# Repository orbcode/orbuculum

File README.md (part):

This is Orbuculum V2.2.0. Bugfixes for 2.2.x will be done in this branch. Development is generally done in feature branches and folded into main as those features mature - those are post 2.2.0.

Version 2.2.0 builds on 2.1.0 and adds several new CPU families, improved client application handling and the start of ETM4 support. Stats and timing are also much improved and the whole communications subsystem has been simplified and streamlined. Most importantly though, we have moved from 'legacy' protocol (basically, the exact same protocol that flows from the chip) for communications to 'orbflow' protocol. Orbflow protocol is an extensible packet oriented protocol which provides a more compact representation of the probe data. By default orbflow is used transparently between orbuculum and client applications. If you have an ORBTrace 1.4.0 or higher version then it is also used for communication from the probe to orbuculum. If you have your own legacy applications, or a version of ORBTrace less that 1.4.0, then the system will fall back to legacy protocol transparently. You can have a hybrid arrangement where some clients use legacy protocol and some use orbflow no problem.  As you might imagine this can quickly become complex so please yell up if any edge cases don't seem to work correctly!

For the full benefit of this version you should be using ORBTrace mini Version 1.4.0 or higher. It will work with earlier versions but you won't get the in probe TPIU stripping or improved probe to host comms protocol support.

The CHANGES file now tells you what's been done recently.

Orbuculum now has an active Discord channel at https://discord.gg/P7FYThy . Thats the place to go if you need interactive help.

An Orbuculum is a Crystal Ball, used for seeing things that would
 be otherwise invisible. A  nodding reference to (the) BlackMagic
 (debug probe), BMP.

You can find information about using this suite at [Orbcode](https://www.orbcode.org), especially the 'Data Feed' section.

**ORBTrace Mini is now available for debug and realtime tracing. Go to [Orbcode](https://www.orbcode.org) for more info.**

The code is in daily use and small issues are patched as they are found. The software runs on Linux, OSX and Windows. Any bugs in a release version are treated as high priority issues. Functional enhancements will also be folded in as time permits. Currently progress is reasonably rapid, and patches are always welcome.

What is it?
===========

Orbuculum is a set of tools for decoding and presenting output flows from
the tracing output pins of a CORTEX-M CPU. Originally it only supported the SWO pin in UART format but it now also
supports hardware for parallel tracing through ORBtrace as well as SWO in UART and Manchester formats.
Numerous types of data can be output through these various
pins, from multiple channels of text messages through to Program Counter samples and even full cycle accurate instruction trace.
Processing these data gives you a huge amount of insight into what is really going on inside
your CPU. The tools are all mix-and-match according to what you are trying to do. The current set is;

* orbuculum: The main mux program which interfaces to the trace probe and then issues a network
interface to which an arbitary number of clients can connect. This is
used as a base interface to the target by other programs in the suite. Generally you configure
this for the TRACE tool you're using and then you can just leave it running. It will grab
data from the target and make it available to clients whenever it can.

* orbcat: A simple cat utility for ITM channel data.

* orbdump: A utility for dumping raw SWO data to a file for post-processing.

* orbmortem: A post mortem analysis tool.

* orbtop: A top utility to see what's actually going on with your target. It can also
generate input files for dot and gnuplot for perty graphics.

* orbtop-rtos: An enhanced version of orbtop with RTOS-aware thread profiling support. Currently
supports  RTOS ( cmsis rtx, etc) and provides per-thread CPU usage statistics, thread state monitoring, and
context switch analysis. Requires connection to OpenOCD for RTOS data extraction.

* orbstat: An analysis/statistics utility which can produce KCacheGrind input files.

* orbtrace: The fpga configuration controller for use with ORBtrace hardware.

* orbzmq: ZeroMQ server.

* orblcd: LCD emulator on the host.

There is also Python support in the [pyorb](https://github.com/orbcode/pyorb) repository.

A few simple use cases are documented in the last section of this
document, as are example outputs from using orbtop to report on the
activity of BMP while emitting SWO packets.

The data flowing from the SWO pin can be encoded
either using NRZ (UART) or RZ (Manchester) formats.  The pin is a
dedicated one that would be used for TDO when the debug interface is
in JTAG mode. We have demonstrated
ITM feeds of around 4.3MBytes/sec on a STM32F427 via SWO with Manchester
encoding running at 48Mbps. SWO with UART encoding is good for 62Mbaud. The encoding of UART
is less efficient than Manchester so those speeds come out largely the same. Users are advised
to use Manchester encoding if their probe supports it because then they don't have to stress about
data speeds (it's autobauding), clock changes or start/stop bits.

The data flowing from the parallel TRACE pins is clocked using a separate TRACECLK pin. There can
be 1-4 TRACE pins which obviously give you much higher bandwidth than the single SWO. Using ORBTrace
we have demonstrated ITM feeds of around 12.5MBytes/sec on a STM32F427 via 4 bit parallel trace. These are not
typos, parallel trace really does run that fast if you've got suitable hardware.

Whatever it's source, orbuculum takes these data flow and makes them accessible to tools on the host
PC. At its core it takes data from the source, decodes it and presents it on a network
interface...both orbflow and legacy protocols are available. The Orbuculum tools don't care if the data
originates from a RZ or NRZ port, SWO or TRACE, or at what speed....that's all the job
of the interface.

At the present time Orbuculum supports ten devices for collecting trace
from the target;

* Black Magic Debug Probe (BMP)
* SEGGER JLink
* generic USB TTL Serial Interfaces
* FTDI High speed serial interfaces
* OpenOCD (Add a line like `tpiu config internal :3443 uart off 32000000` to your openocd config to use it...more detailed configuration info at the bottom of this document)
* PyOCD (Add options like `enable_swv: True`, `swv_system_clock: 32000000` to your `pyocd.yml` to use it.)
* ECPIX-5 ECP5 Breakout Board for parallel trace
* Anything capable of saving the raw SWO data to a file
* Anything capable of offering SWO on a TCP port
* ORBTrace Mini (V1.4.0 or higher for orbflow support)

Note that current support for the ECPIX-5 breakout board is based on the original BOB, the designs for which
are in the orbtrace_hw repository. BOB2 support will be added when we get around to it (probably when we decide we
need USB3 support...unlikely to be yet a while).

For 'normal' users we highly reccomend the ORBTrace mini probe for the best experience using this stuff. That's
not particularlly to make money (the designs are in the orbtrace_hw directory...feel free to build you own), but
because that hardware has been tuned for the job to be done. Getting an ORBTrace allows you to participate in the
project, it's not a product yet, although it does work remarkably well.

gdb setup files for each device type can be found in the `Support` directory. You'll find
example get-you-going applications in the [Orbmule](https://github.com/orbcode/orbmule) repository including
`gdbinit` scripts for OpenOCD, pyOCD and Black Magic Debug Application (BMDA). There are walkthroughs for lots of examples
of the use of the suite at [Orbcode](https://orbcode.org).

When using SWO Orbuculum can use, or bypass, the TPIU. The TPIU adds overhead
to the datastream, but provides better synchronisation if there is corruption
on the link. To include the TPIU in decode stack, provide the -T
option on the orbuculum command line. If you don't provide it, and the ITM decoder sees
TPIU syncs in the datastream, it will complain. This is deliberate
after I spent two days trying to find an obscure bug 'cos I'd left the `-T` option off. If you don't specify, then
only TPIU stream 1 is decoded over legacy protocol, so use the `-tx` option to add additional streams. If you have an
end to end orbflow configuration with the probe stripping the TPIU framing then all streams are passed transparently
throughout the system and you don't need to worry about `-T` or `-tx`.

Beware that in parallel trace the TPIU is mandatory...it must be stripped somewhere in the system; Either by the probe or by `orbuculum`. ORBTrace 1.4.0 and above does that automatically. Other probes...not so much.

For legacy applications orbuculum makes the TPIU data streams available on
consecutive TCP/IP ports...so `-t 1,2` would put stream 1 data out over TCP port 3443 and stream 2 over 3444, by default. Do
not leave the first number out if you only want output from the second stream...that won't end well.  orbflow (on port 3402 by default)
supports all streams simultaneously, putting them under separate 'tags'.

When in NRZ (UART) mode the SWO data rate that comes out of the chip _must_
match the rate that the debugger expects. On the BMP speeds of
2.25Mbps are normal, TTL Serial devices tend to run a little slower
but 921600 baud is normally acheivable. On BMP the baudrate is set via
the gdb session with the 'monitor traceswo xxxx' command. For a TTL
Serial device its set by the Orbuculum command line.  Segger devices
can normally work faster, but no experimentation has been done to
find their max limits, it's probably dependent on the specific JLink
you are using, and the available baudrates appear to be quantised.
ORBTrace Mini can operate with UART encoded SWO at any speed from 125Kbits/sec up to 62MBits/sec. It
also supports Manchester encoded SWO at up
to 48Mbps. The advantage of Manchester encoding is that there's no speed matching needed to use it, and it should
continue to work correctly even if the target clock speed changes (e.g. when it goes
into a low power mode). This is a good thing, and is the way we normally use SWO for day-job.

Configuring the Target
======================

Generally speaking, you will need to configure the target device to output
SWO or parallel data. You can either do that through program code, or through magic
incantations in gdb. The gdb approach is flexible but a bit clunky. novakov has created
the libtrace repository which includes all the code needed to configure your target
directly via progam code if you prefer to set things up that way.

If you want to go via gdb then in the support directory you will find a script `gdbtrace.init` which contains a
set of setup macros for the SWO functionality. Full details of how to set up these
various registers are available from [Arm](https://static.docs.arm.com/ddi0403/e/DDI0403E_B_armv7m_arm.pdf) and
you've got various options for the type of output generated, its frequency and it's content.

Using these macros means you do not need to change your program code to be able to use
facilities like `orbtop`. Obviously, if you want textual trace output, you need to generate
that in your program!

Information about the contents of this file can be found by importing it into your
gdb session with `source gdbtrace.init` and then typing `help orbuculum`. Help on the
parameters for each macro are available via the help system too (e.g. `help enableSTM32SWO`).

In general, you will configure orbuculum via your local `.gdbinit` file. Several example files are
also in the Support directory. 

Anyway, generically, a configuration looks like this;

    source Support/gdbtrace.init            <---- Source the trace specific stuff
    target extended-remote /dev/ttyACM0     <-
    monitor swdp_scan                       <-
    file ofiles/firmware.elf                <-
    attach 1                                <---- Connect to the target
    set mem inaccessible-by-default off     <-
    set print pretty                        <-
    load                                    <---- Load the program

    start                                   <---- and get to main

    # ---------- Using Stm32F1 as debuggee---------------------------
    enableSTM32SWO                          <*--- turn on SWO output pin on CPU
    # ----------ALTERNATIVELY, for Stm32F4 as debuggee----------------
    enableSTM32SWO 4                        <*--- turn on SWO output pin on CPU
    # ----------END OF ALTERNATIVE-----------------------------------

    # ---------- EITHER, IF USING A BLUEPILL-------------------------
    monitor traceswo 2250000                <*--- wakeup tracing on the probe
    prepareSWO SystemCoreClock 2250000 1 0  <*--- Setup SWO timing (Bluepill case)

    # ----------ALTERNATIVELY, FOR GENUINE BMP-----------------------
    monitor traceswo                        <*--- Enable BMP traceswo output
    prepareSWO SystemCoreClock 200000 0 1   <*--- Setup SWO timing (BMP case)
    # ----------END OF ALTERNATIVE-----------------------------------

    dwtSamplePC 1                           <-
    dwtSyncTap 3                            <-
    dwtPostTap 1                            <-
    dwtPostInit 1                           <-
    dwtPostReset 15                         <-
    dwtCycEna 1                             <---- Configure Data Watch/Trace

    ITMId 1                                 <-
    ITMGTSFreq 3                            <-
    ITMTSPrescale 3                         <-
    ITMTXEna 1                              <-
    ITMSYNCEna 1                            <-
    ITMEna 1                                <---- Enable Instruction Trace Macrocell

    ITMTER 0 0xFFFFFFFF                     <---- Enable Trace Ports
    ITMTPR 0xFFFFFFFF                       <---- Make them accessible to user level code

Alternatively, if you're using parallel trace via ORBTrace remove the lines marked <*- above and
replace them with the following;

    enableSTM32TRACE                         <---- Switch on parallel trace on the STM32

...be careful to set the trace width to be the same as what you've configured on the FPGA. It defaults to four bits wide. While
we're here it's worth mentioning the `startETM` command too, that outputs tracing data. That is
needed for `orbmortem`.

In-code configuration
---------------------
Trace components may also be configured directly from code running on the target. Such an
approach is useful for setting up more invasive tracing or logging output.

CMSIS-compatible headers, provided by many chip vendors, include all necessary type definitions and constants.
However they are not the most straightforward, so it might be easier to use Orbcode's libtrace
library: https://orbcode.github.io/libtrace/

Building on Linux
=================

Dependencies
------------
* libusb-1.0
* cmake
* pkg-config
* libczmq5-dev
* ncurses-dev
* libsdl2-dev
* libzstd-dev
* libelf-dev
* libcapstone-dev

On Debian 12, at least, the following command should get you everything you need;

```
sudo apt-get install libusb-1.0-0-dev cmake pkg-config libczmq5-dev ncurses-dev libelf-dev libsdl2-dev libzstd-dev libcapstone-dev
```
 
Build
-----

In general you'll find recent binaries available for your platform as build artifacts from the Github Actions we run for CI.
Just go to the 'Actions' menu in github and then grab the artifacts from the latest builds. That's not the preferred method,
but it's a quick-and-dirty solution.

If you do want to build the system, then the sequence is:

```
>meson setup build
>ninja -C build
```

You may need to change the paths to your libusb files, depending on how well your build environment is set up. You might also want to change the install path, which defaults to putting everything under `/usr/local`, by passing the appropriate path to meson with a command line such as `meson setup --prefix=/usr build`...we've had some feedback that Arch doesn't find libraries under `/usr/local/lib`, for example. It's also worth noting that some releases of Ubuntu come with a pretty old version of meson so if you get errors you may need to install a more recent one via pip.

Permissions and Access
----------------------
A udev rules files is included in ```Support/60-orbcode.rules``` The default installation will have already installed this to either `/usr/local/lib/udev/rules.d` or `/usr/lib/udev/rules.d`, but you may prefer to install it to ```/etc/udev/rules.d``` by hand, if required.

Building on OSX
===============

* `brew install libusb zmq sdl2 libelf`

If you are on an Intel Mac: 

```
export LDFLAGS="-L/usr/local/opt/binutils/lib"
export CPPFLAGS="-I/usr/local/opt/binutils/include"
```

If you are on an Apple Silicon Mac, do not export the environment variables.

You can also see notes under [Issue #63](https://github.com/orbcode/orbuculum/issues/63) from Gasman2014 about building on a M1
Mac. You need to watch out for Homebrew binutils...on an Apple Silicon Mac you must use the Apple binutils (e.g. avoid the above environment export
so that x86 homebrew binutils is not used) or you will get linker errors.

And finally,

```
meson setup build
ninja -C build
```

Building on FreeBSD
===================
Install dependencies:

* `pkg install capstone libzmq3 ncurses libelf ninja meson`

then build as normal:

```
>meson setup build
>ninja -C build
```

Note that you will have to alter permissions of the device in `/dev/usb` (run `usbconfig` to find the numbers). This could be automated with a `devd` file.

Building on Windows
===================

MinGW-w64 from MSys2 is recommended as the environment for building the Windows distribution. The easiest way to get proper MSys2/MinGW-w64 environment is to use Chocolatey (https://community.chocolatey.org/packages/msys2).

Dependencies
------------
* mingw-w64-x86_64-libusb
* mingw-w64-x86_64-libelf
* mingw-w64-x86_64-zeromq
* mingw-w64-x86_64-meson
* mingw-w64-x86_64-SDL2
* mingw-w64-x86_64-toolchain (Ada and Fortran are not needed)
* ninja
* git

In MSys2/MinGW-w64 run command: `pacman -S mingw-w64-x86_64-meson mingw-w64-x86_64-SDL2 ninja mingw-w64-x86_64-libusb mingw-w64-x86_64-toolchain mingw-w64-x86_64-zeromq git` to install all required dependencies.

Note that at the moment the Windows build is using a forked libusb because of constraints in the upstream build opening multiple interfaces on the same device at the same time. Hopefully that situation is only temporary.

Build
-----

The command line to build the Orbuculum tool suite is:

```
>meson setup build
>ninja -C build
```

In order to get single folder with Orbuculum and MinGW dependencies run:

```
>meson configure build --prefix A:/
>meson install -C ./build --destdir ./install --strip
```

`--prefix A:/` is required to workaround how Meson constructs the install directory. Without it a deeply nested path will be generated instead of the clean `build/install`.

Orbuculum executables along with MinGW-w64 dependencies will be installed into `build/install` and can be transfered to different machine or used outside of MSys2 shell.

Communications
==============

Originally orbuculum provided a TCP/3443 port to which an arbitary number of clients could connect
and each one would receive a clean copy of the data from the probe. Optionally, the TPIU framing could
be stripped off by orbuculum so that individual clients didn't have to do it and each TPIU stream would then
appear on consecutive ports; Generally, that means that ITM messages appeared on TCP/3443 and ETM on TCP/3444.

Some debug drivers (e.g. openocd, pyocd) can now create an orbuculum-compatible interface on TCP/3443, which
allows you to connect the rest of the suite to that directly, without needing to use the orbuculum mux itself.
These really only appear to support ITM at the moment.

However, times have moved on. Passing all those data through transparently was wasteful as a fair few messages 
were 'nothing to see here'. Orbuculum now supports a new protocol, orbflow (OFLOW). Orbflow is normally carried on TCP/3402. 
It is a bit more intelligent than simply passing through the messages from the probe. It turns the stream of data into
COBS encoded sequenced messages with defined boundries and it also removes the redundant data. When used
in conjunction with an ORBTrace 1.4.0 or higher probe the orbflow messages are created in the probe itself, providing a further
performance improvement.

Basically, all of this is mostly transparent to the regular end user. Orbflow is automatically used for communication
between orbuculum and its clients if it's available, and Orbuculum still provides the TCP/3443 port it always did,
which you can connect to in the same way as you used to if you've got custom clients. Orbflow will give you a performance
improvement, but it's otherwise transparent to users.

There are come slight changes to the command line options though. Historically, when using TPIU decoding,
you had to specify the channels to be decoded with an option like `-T 1,2`. You now simply need to tell orbuculum
which tags to reflect over legacy protocol using `-t 1,2` and, if your probe doesn't remove TPIU framing automatically, specify the `-T`
option on its own....if you try to specify the `-T` option and you've got an ORBTrace that supports Orbflow protocol
then you'll get a warning because TPIU framing removal is done automatically in the probe in that case, so you
don't generally need it....it's still possible to do it because there are some edge cases where it's useful, but you will
know why you need it if you need it, and you'll know to ignore the warning. If you're using end-to-end orbflow then you can
ignore the `-T` and `-tx` options altogether, although you might still need to tell the client which tag to access.

Note that individual clients cannot now strip TPIU. This was a fringe requirement which can still be met by piping via
`orbuculum` first. Clients are simpler and smaller as a result of removing this.

Why have we made this change? Well, decoding TPIU on the probe saves a huge amount of bandwidth, and moving to the
tag based approach lets us convey other information from the probe too such as timestamps, voltages and currents.

Using
=====

The command line options for Orbuculum are available by running
orbuculum with the -h option.

Simply start orbuculum with the correct options for your trace probe and
then you can start or stop other utilities as you wish. A typical command
to run orbuculum would be;

```$ orbuculum --monitor 1000```

In this case, because no source options were provided on the command line, input
will be taken from a Blackmagic probe USB SWO feed, or from an ORBTrace mini if it can find one. If multiple
probes are found you will get the option to choose between them. To avoid this choice, add any unique part of the
serial number for the probe you want to use on the command line.
The command above will start the daemon with a monitor reporting interval of 100ms.  Orbuculum exposes TCP ports 3402 and 3443 to which
network clients can connect. 3402 delivers orbflow, 3443+x deliver raw frames. Both will relay to any
client that is connected (such as orbcat or orbtop).
The practical limit to the number of clients that can connect is set by the speed of the host machine....but there's
nothing stopping you using another one on the local network :-)  Orbuculum can optionally call out to `orbtrace` when a
probe first connects. this is typically used to set configuration parameters for the problem. For example, if you've got an
orbtrace mini and you want to switch on power to your target and configure it for Manchester SWO, a suitable command would be;

```$ orbuculum --monitor 1000 --orbtrace '-p vtref,3.3 -e vtref,on'```

...arranging `orbtrace` to get called from `orbuculum` means the probe will be re-initialised if it gets disconnected at any time.
Note that the `--orbtrace` bit is providing options through to
the `orbtrace` application, so you need to look at the command line options for that to make sensible selections.

Information about `orbuculum` command line options can be found with the -h
option.  Orbuculum itself is specifically designed to be 'hardy' to probe and
target disconnects and restarts (y'know, like you get in the real
world). In general the other programs in the suite will stay alive while
`orbuculum` itself is available.  The intention is to give you useful information whenever it can be
obtained.  Orbuculum does _not_ require gdb to be running, but you may need a
gdb session to start the output.  BMP needs traceswo to be turned on
at the command line before it capture data from the SWO pin, for example.

Its worth a quick word about how the orbuculum mux interacts with clients. Pretty obviously, clients need to keep
up with the flow of data from a probe. For the case that a client doesn't then it will be disconnected. It's then
free to reconnect again.  When reading from a file (and we don't have the same timing constraints as we do when
talking to a probe) then a slow client will be accomodated by slowing down the entire flow and waiting for the client
to catch up. The easiest way to see this in action is to pause a client (e.g. `CTRL-Z` on an orbcat session)...you will
see orbuculum's data transfer go to zero. When you re-start the client (e.g. `fg` to bring it back into the foreground)
then it will carry on from where it left off and no client will lose data.

Command Line Options
====================

For `orbuculum`, the specific command line options of note are;

 `-a, --serial-speed: [serialSpeed]`: Use serial port and set device speed.

 `-E, --eof`: When reading from file, ignore eof.

 `-f, --input-file [filename]`: Take input from file rather than device.

 `-h, --help`: Brief help.

 `-l, --listen-port:   <port> for incoming ORBFLOW connections (defaults to 3402). Legacy port always starts +41 away from this (i.e. 3443 by default).

 `-m, --monitor`: Monitor interval (in ms) for reporting on state of the link. If baudrate is specified (using `-a`) and is greater than 100bps then the percentage link occupancy is also reported. Minimum of 500ms.

 `-n, --serial-number`: Set a specific serial number for the ORBTrace or BMP device to connect to. Any unambigious sequence is sufficient. Ignored for other probe types.

  `-o, --output-file [filename]`: Record trace data locally. This is unfettered data directly from the source device (with a 16 byte magic header). This can be useful for replay purposes or other tool testing.

  `-O "<options>"`: Run orbtrace on each detected connection of a probe, with the specified options.

  `-p, --serial-port [serialPort]`: to use. If not specified then the program defaults to Blackmagic probe.

  `-P, --pace [microseconds>]`: delay in block of data transmission to clients. Used when source is a file, ignored otherwise.

  `-s, --server [address]:[port]`: Set address for explicit TCP Source connection, (default none:2332).

  `-T, --tpiu`: Remove TPIU formatting from incoming data stream. TPIU is removed from tag 1 when source is an ORBTrace mini 1.4.0 or higher and a warning is printed.

  `-t, --tag x,y,...`: List of streams to decode (and onward route) from the probe (low stream numbers are TPIU channels). *By default only stream 1 (ITM) is routed over legacy protocol, add additional streams via this command*

Orbzmq
------
`orbzmq` is utility that connects to orbuculum over the network and outputs data from various ITM HW and SW channels that it finds. This output is sent over a [ZeroMQ](https://zeromq.org/) PUBLISH socket bound to the specified URL. Each published message is composed of two parts: **topic** and **payload**. Topic can be used by consumers to filter incoming messages, payload contains actual message data - for SW channels formatted or raw data and predefined format for HW channels.

A typical command line would be like:

```> orbzmq -l tcp://localhost:1234 -c 0,text,%c -c 1,raw, -c 2,formatted,"Value: 0x%08X\n" -e AWP,OFS,PC -v 1```

`orbzmq` will create a ZeroMQ socket bound to address `tcp://*:3442` (which means, all interfaces, tcp port 3442) and publish messages with topics: `text`, `raw`, `formatted`, `hweventAWP`, `hweventOFS` and `hweventPC`.

A simple python client can receive messsages in the following way:
```python
import zmq

ctx = zmq.Context()
sock = ctx.socket(zmq.SUB)
sock.connect('tcp://localhost:3442')
sock.setsockopt(zmq.SUBSCRIBE, b'raw')
sock.setsockopt(zmq.SUBSCRIBE, b'formatted')
sock.setsockopt(zmq.SUBSCRIBE, b'hwevent') # subscribe to all hwevents

while True:
    [topic, msg] = sock.recv_multipart()
    if topic == b'raw':
        decoded = int.from_bytes(msg, byteorder='little')
        print(f'Raw: 0x{decoded:08X}')
    elif topic == b'formatted':
        print(msg.decode('ascii'),end="")
    elif topic.startswith(b'hwevent'):
        print(f'HWEvent: {topic} Msg: {msg}')
```

Command line options are:

 `-c, --channel [Topic],[Name],[Format]`:      of channel to populate (repeat per channel)

 `-e, --hwevent [event1],[event2]`:      Comma-separated list of published hwevents (Use `all` to include all hwevents)

 `-E, --eof`:          Terminate when the file/socket ends/is closed, or attempt to wait for more / reconnect

 `-f, --input-file [filename]`:   Take input from specified file

 `-h, --help`:         This help

 `-n, --itm-sync`:     Enforce sync requirement for ITM (i.e. ITM needsd to issue syncs)

 `-s, --server [server]:[port]`:       to connect to

 `-t, --tag [numberl]`:         Specify tag to decode (normally 1)

 `-v, --verbose [level]`:      Verbose mode 0(errors)..3(debug)

 `-V, --version`:      Print version and exit

 `-z, --zbind [url]`:         ZeroMQ bind URL

Orblcd
------

orblcd lets you emulate an LCD panel on a host computer. This is useful for test and development purposes.
Communication between the target and host occurs over two ITM channels, using a protocol defined in `orblcd_protocol.h`. You need
to share a common version of this file between `orblcd` and your target.

1, 8, 16 and 24/32 bit lcd depths are supported. 1 and 24/32 bit are well tested, but 16 and 8 need a little bit more proving. There
is no functional difference between 24 and 32 bit operation (there is no Alpha channel, although it's trivial to add if you want it).

On the target side, all that needs to be done is to tell the host the characteristics of the panel;

```
ITM_Send32(LCD_COMMAND_CHANNEL,ORBLCD_OPEN_SCREEN(XSIZE*8,YSIZE*16,ORBLCD_DEPTH_1));
```

Once the characteristics have been established, this same command will render any data received.

Once the link is established, then the target simply streams data to the host;

```
ITM_Send32(LCD_DATA_CHANNEL,<data word>);
```

For 1, 8 and 16 bit lcds multiple pixels are encoded into a single 32-bit word. Any pixels left at the end of a line are discarded. If that
doesn't suit, then use the 24/32 bit channel mode to transfer pixels.

There is no limit on the amount of data that may be sent - the screen will not be rendered at the host until the next `OPEN_SCREEN` message is received. The target is free to move around the virtual lcd panel to update the contents anywhere it wishes (and new manipulation commands may be added into the shared header file `orblcd_protocol.h`).

By operating in this way, even if the host connects late it will quickly establish good quality comms with the target. See
the `vidout` example in orbmule for an example of how to use the utility for 1-bit operation, or build the `lcd_demo` application
with the orblcd video device as output for a 24-bit example with;

```
make GRAPHIC_LIBRARY=ORBLCD
```

 `-c, --channel [Number]`: of first channel in pair containing display data (channel+1 is the command channel).

 `-f, --input-file [filename]`: Take input from specified file.
 
 `-h, --help`: Get help.

 `-n, --itm-sync`: Enforce sync requirement for ITM (i.e. ITM needsd to issue syncs).

 `-s, --server [Server]:[Port]`: to use.

 `-S, --sbcolour [Colour]`: to be used for single bit renders, ignored for other bit depths.

 `-t, --tag [number]`: Decode specified tag (normally 1).

 `-v, --verbose [level]`: Verbose mode 0(errors)..3(debug).

 `-V, --version`: Print version and exit.
 
 `-z, --size [Scale(float)]`: Set relative size of output window (normally 1).

Orbcat
------

orbcat is a simple utility that connects to orbuculum over the network and
outputs data from various ITM HW and SW channels that it finds.  This
output is sent to stdout so the program is very useful for providing direct
input for other utilities.  There can be any number of instances of orbcat
running at the same time, and they will all decode data independently as they all get
a seperate networked data feed.  A
typical use case for orbcat would be to act as a stdin for another program...an example
of doing this to just replicate the data delivered over ITM Channel 0 would be

`orbcat -c 0,"%c"`

...note that any number of `-c` options can be entered on the command line, which
will combine data from those individual channels into one stream. Command line
options for orbcat are;

 `-c, --channel [Number],[Format]`: of channel to populate (repeat per channel) using printf
     formatting. Note that the `Name` component is missing in this format because
     orbcat does not create fifos. **beware not to have any extraneous spaces in this option,
     that generally ends up not doing what you want as its interpreted as a new option.**

 `-C, --cpufreq [Frequency in KHz]`: Set (scaled) speed of the CPU to convert CPU timestamps into time timestamps. When
      this option is set `-Ts` and `-Tt` will generate output in milliseconds and thousandths of a millisecond
      for an effective resolution of 1us, provided your target has been configured to generate timestamps. **Note
      the frequency you set should be scaled according to the setting in the ITM Control register (/1, /4,
      /16 or /64).**

 `-E, --eof`: When reading from file, terminate when file exhausts, rather than waiting for more data to arrive.

 `-f, --input-file [filename]`: Take input from specified file (CTRL-C to abort from this).

 `-g, --trigger [char]:` Character to use to trigger timestamp generation. Default is newline. Target character is
     removed from the output stream and replaced with a newline followed by a timestamp in the format specified
     by `-Tx`. Control characters (e.g. newline \\n or tab \\t) can be specified as the trigger.
    
 `-h, --help`: Brief help.

 `-n, --itm-sync`: Enforce sync requirement for ITM (i.e. ITM needsd to issue syncs)

 `-s --server [server]:[port]`: to connect to. Defaults to `localhost:3443` to connect to the orbuculum daemon. Use `localhost:2332` to connect to a Segger J-Link, or whatever other combination applies to your source.

 `-t, --tag [number]`: Specify tag to decode.

 `-T, --timestamp [a|r|d|s|t]`: Add absolute, relative (to session start), delta, system timestamp or system timestamp delta to output. Note that
    system timestamp and system timestamp delta are only available if your target is generating timestamps, otherwise they will read back
    as zero. A timestamp is generated on reception of the first character following the trigger char (Set with `-gx`). This means that even if the
    output is lengthy it is timestamped from when it started.

 `-v, --verbose [x]`: Verbose mode level 0..3.

 `-w, --window [string]`: Title for on-screen window.

 `-x, --exceptions`: Include exception information in output, in time order
 
Orbtop
------

Orbtop connects to orbuculum over the network and
samples the Program Counter to identify where the program is spending its time. By default
it will update its statistical output once per second. For code that matches to a function
the the source file it will totalise all of the samples to tell you how much time is being
spent in that function.  Any samples that do not match to an identifiable function are
reported as 'Unknown'.

As with Orbcat there can be any number of instances of orbtop running at the same time,
which might be useful to perform sampling over different time horizons. A typical invocation
line for orbtop would be;

`orbtop -e ~/Develop/STM32F103-skel/ofiles/firmware.elf`

...the pointer to the elf file is always needed for orbtop to be able to recover symbols from.

One useful command line option for orbtop (and indeed, for the majority of the rest of the
suite) is `-s localhost:2332`, which will connect directly to any source you might have exporting
SWO data on its TCP its port, with no requirement for the orbuculum multiplexer in the way. If
you set the source explicitly, you also need to set the protocol explicitly using `-p`.

Command line options for orbtop are;

 `-c, --cut-after [num]`: Cut screen output after number of lines.

 `-d, --del-prefix [DeleteMaterial]`: to take off front of filenames (for pretty printing).

 `-D, --no-demangle`: Switch off C++ symbol demangling (on by default).

 `-e, --elf-file`: Set elf file for recovery of program symbols. This will be monitored and reloaded if it changes.

 `-E, --exceptions`: Include exception (interrupt) measurements.

 `-f, --input-file [Filename]`: Take input from specified file

 `-g, --record-file [LogFile]`: Append historic records to specified file on an ongoing basis.

 `-h, --help`: Brief help.

 `-I, --interval [Interval]`: Set integration and display interval in milliseconds (defaults to 1000 ms)

 `-j, --json-file [filename]`: Output to file in JSON format (or screen if <filename> is '-')

 `-l, --agg-lines`: Aggregate per line rather than per function

 `-n, --itm-sync`: Enforce sync requirement for ITM (i.e. ITM needs to issue syncs)

 `-o, --output-file [filename]`: Set file to be used for output history

 `-O, --objdump-opts [opts]`: Set options to pass directly to objdump

 `-p, --protocol [OFLOW|ITM]`: Protocol to communicate. Must be set explicitly if -s is set

 `-P, --pace <microseconds>`: Delay in block of data transmission to clients

 `-r, --routines <routines>`: Number of lines to record in history file

 `-R, --report-file [filename]`: Report filenames as part of function discriminator

 `-s, --server [server]:[port]`: to connect to. Defaults to localhost:3443

 `-t, --tag [number]`: Specify tag to decode. Defaults to 1.

 `-v, --verbose [x]`: Verbosity level 0..3.

It is worth a few notes about interrupt measurements. orbtop can provide information about the number of
times an interrupt is called, what its maximum nesting is, how many 'execution ticks' it's active for
and what the spread is of those. Here's a typical combination output for a simple system;

```
 98.25%     1911 ** SLEEPING **
  0.25%        5 uart_xmitchars
  0.20%        4 up_serialin
  0.10%        2 up_doirq
  0.10%        2 up_interrupt
  0.10%        2 up_restoreusartint
  0.10%        2 uart_pollnotify
  0.10%        2 uart_write
  0.10%        2 nxsem_post
-----------------
 99.30%     1932 of 1945 Samples

 Ex |   Count  |  MaxD | TotalTicks  |  AveTicks  |  minTicks  |  maxTicks
----+----------+-------+-------------+------------+------------+------------
 11 |        1 |     1 |        263  |        263 |       263  |       263
 15 |      100 |     1 |      10208  |        102 |       100  |       210
 53 |      210 |     1 |      44752  |        213 |        97  |       479

[--TH] Interval = 1002ms / 7966664 (~7950 Ticks/ms)
```

The top half of this display is the typical 'top' output, the bottom half is a table of
active interrupts that have been monitored in the interval. Note that outputs are
given in terms of 'ticks', and the number of cpu cycles that correspond to a tick
is set by `ITMTSPrescale`. You will also need to set `dwtTraceException` and
`ITMTSEna` to be able to use this output mode. Note that if the debug channel is over-full
then these are the first data the target will discard and the information presented on this
panel cannot be trusted. This is indicated by a 'V' in the first column of the flags display.

Orbmortem
---------

To use orbmortem you must be using a parallel trace source such as ORBTrace Mini, and it must be
configured to stream parallel trace info (clue; the `startETM` option). Orbmortem is not thoroughly
tested and contributions on solidifying it are welcome.

The command line options of note are;

 `-a, --alt-addr-enc`: Don't use alternate address encoding. Select this if decodes don't seem to arrive correctly. You can discover if you need this option by using the `describeETM` command inside the debugger.

 `-b, --buffer-len [Length]`: Set length of post-mortem buffer, in KBytes (Default 32 KBytes)

 `-c, --editor-cmd [command]`: Set command line for external editor ( %%f = filename, %%l = line). A few examples are;

     * emacs; `-c emacs "+%l %f"`
     * codium/VSCode; `-c codium  -g "%f:%l"`
     * eclipse; `-c eclipse "%f:%l"`

 `-D, --no-demangle`: Switch off C++ symbol demangling

 `-d, --del-prefix [String]`: Material to delete off front of filenames

 `-e, --elf-file [ElfFile]`: to use for symbols and source

 `-E, --eof`: When reading from file, terminate at end of file rather than waiting for further input

 `-f, --input-file [filename]`: Take input from specified file rather than live from a probe (useful for ETB decode)

 `-h, --help`: Provide brief help

 `-p, --trace-proto [protocol]`: to use, where protocols are MTB or ETM35 (default). Note that MTB only makes sense from a file.

 `-s, --server [Server:Port]`: to use

 `-t, --tag [number]`: Specify tag to decode, defaults to 2.

Once it's running you will receive an indication at the lower right of the screen that it's capturing data. Hitting `H` will hold the capture and it will decode whatever is currently in the buffer. More usefully, if the capture stream is lost (e.g. because of debugger entry) then it will auto-hold and decode the buffer, showing you the last instructions executed. You can use the arrow keys to move around this buffer and dive into individual source files. Hit the `?` key for a quick overview of available commands.

Reliability
===========

A whole chunk of work is constantly being done to make sure the dataflow over both the
SWO link and parallel Trace is reliable....but it's pretty dependent on the debug
interface itself.  The TL;DR is that if the interface _is_ reliable
then Orbuculum will be. There are factors outside of our control
(i.e. the USB bus you are connected to) that could potentially break the
reliabilty but there's not too much we can do about that since the SWO
link is unidirectional (no opportunity for re-transmits). Using ORBTrace We have transmitted
gigabytes of date over SWO and TRACE links with no errors, which is pretty impressive
when you consider the speeds we are talking about and the fact that there is no
error detection or correction on the link itself.

ORBTrace is capable of sustained 390Mbits/sec transfer over a clean USB link. Make sure you've got
no hubs or contending devices on the USB bus that ORBTrace is attached to in order to reach these speeds.

As one example, ORBTrace Mini was configured with a target application sending out repeated strings at maximum speed
over a 48Mbps SWO/Manch channel for an extended period of time. They were then collated and sorted by uniqueness, as follows;

```
$ time orbcat -c 0,"%c" | sort | uniq -c
      1 ABCDEFGHIJKLMNOPQRST
2385153869 ABCDEFGHIJKLMNOPQRSTUVWXYZ_*_abcdefghijklmnopqrstuvwxyz

real    490m37.616s
user    82m15.087s
sys    11m2.847s
```

That is 124.4GBytes of user to user transfer, 155.5GBytes of line transfer with no errors at 5.4MBytes/sec line,
4.32MBytes/sec user-to-user, assuming my math is holding up. If the wiring is reliable, the
link will be.  The equivalent test on the same chip using 4 bit parallel TRACE gives a user-to-user data rate
of around 12.5MBytes/sec...at that point you're limited by the speed the CPU can put data out onto line rather
than the capacity of the link itself.

Using SWO in Battle
===================

SWO gives you a number of powerful new capabilities in your debug
arsenal. Here are a few examples....if you have more to add please
send us an email, or go take a look at [orbcode.org](https://orbcode.org).

Multi-channel Debug
-------------------

The easiest and most obvious use of SWO is to give you multi-channel
debug capability. By adding multiple '-c' definitions to the orbuculum
comand line you can create multiple fifos which will each emit data of
interest. So, for the simple case of two distinct serial streams,
something like the following will suffice;

`-c 0,out0,"%c" -c 1,out1,"%c"`

...this will create two fifos in your output directory, `out0` and
`out1`, each with distinct output data.  By default the CMSIS provided
`ITM_SendChar` routine only outputs to channel0, so you will need a
new routine that can output to a specified channel. Something like;

    static __INLINE uint32_t ITM_SendChar (uint32_t c, uint32_t ch)
    {
      if ((CoreDebug->DEMCR & CoreDebug_DEMCR_TRCENA_Msk)  &&      /* Trace enabled */
          (ITM->TCR & ITM_TCR_ITMENA_Msk)                  &&      /* ITM enabled */
          (ITM->TER & (1ul << c)        )                    )     /* ITM Port c enabled */
      {
        while (ITM->PORT[c].u32 == 0);
        ITM->PORT[c].u8 = (uint8_t) ch;
      }
      return (ch);
    }

Now, this works perfectly for chars, but you can also write longer
values into the transit buffer so if, for example, you wanted to write
32 bit values from a calculation, just update the routine to take
int32_t and change the channel definition to be something more like
`-c 4,calcResult,"%d"`. You'll find example routines in the orbmule/examples/simple repository.

Mixing Channels
---------------

It gets more complicated when you want to mix output from
individual channels together. In this circumstance you can either
write a bit of script to merge the channels together, or you can use
`orbcat` to do the same thing from the command line. So if, for
example, you wanted to merge the text from channel0 with the 32 bit values
from channel 4, an orbcat line such as this would do the job;

`orbcat -c 0,"%c" -c 4,"\nResult=%d\n"`

...its obvious that the formatting of this buffer is completely
dependent on the order in which data arrive from the target, so you
might want to put some differentiators into each channel to
keep them distinct - a typical mechanism might be to use commas to
seperate the flows into different columns in a CSV file.

Multiple Simulteneous Outputs
-----------------------------

Orbuculum will place fifos for any defined channels (plus the hardware event
channel) in the specified output directory. It will simulteneously
create a TCP server to which an arbitary number of clients can
connect. Those clients each decode the data flow independently of
orbuculum, so you can present the data from the target simulteneously
in multiple formats (you might log it to a file while also processing
it via a plot routine, for example).  You can also use the source code for orbcat or
orbtop as the basis for creating your own specific decoders
(and I'd really appreciate a copy to fold into this suite too please!).

Using Orbtop
------------
Orbtop is an example client to orbuculum which processes the PC
sampling information to identify what routines are running at any
point in time.  This is essential information to understand what your
target is actually doing and once you've got this data you'll find you
become addicted to it! Just running orbtop with the details of your
target binary is enough for orbtop to
do its magic (along with information about the configuration of the
incoming SWO stream, of course);

`orbtop -t -i 9 -a -e firmware.elf`

orbtop can aggregate per function or per program line. By default it aggregates
per function but to work per-line just add the `-l` option...usually that gives you
too much information though.

The amount (and indeed, presence) of sample data is set by a number of
configuration options. These can be set from program code, but it's
more flexible to set them from gdb. The main ones are;

* `dwtSamplePC` : Enable or disable Program Counter sample generation
* `dwtPostTap` : Set the count rate for the PC interval counter at
either bit 6 or bit 10 of the main CPU clock.
* `dwtPostInit` : set the initial value for the PC interval counter
(this defines when the first sample is taken....you've got to be
pretty precise if this is important to you!).
* `dwtPostReset` : Set the reload value for the PC Interval Counter
(higher values = slower counting).
* `dwtCycEna` : Enable the cycle counter input (i.e. switch the whole
thing on). You won't get far without this set!

The maximum speed at which you can generate samples is defined by the
speed of your SWO connection but, with a 72MHz CPU, the slowest
settings (`dwtPostTap 1` and `dwtPostReset 15`) still generate about
4000 samples per second, so you will get useful information at that
level of resolution. There is a risk that you could miss frequent, but
short, routines if you're running too slow, so do vary the speeds to
make sure you get consistent results...on the other hand running too
fast will lead to flooding the SWO and potentially missing other
important data such as channel output.  You do not need to restart
orbuculum or orbtop in order to change the parameters in gdb - just
CTRL-C, change, and restart. With a setting of `dwtPostReset 1` there
are no overflows when using a async interface at 2.25Mbps, which equates
to 35200 Program Counter samples per second.

Here's a typical example of orbtop output for a Skeleton application based
on FreeRTOS with USB over Serial (CDC) support. This table is updated once per second;

     97.90%     4308 ** Sleeping **
      1.25%       55 USB_LP_CAN1_RX0_IRQHandler
      0.20%        9 xTaskIncrementTick
      0.13%        6 Suspend
      0.09%        4 SysTick_Handler
      0.06%        3 Resume
      0.06%        3 __WFI
      0.04%        2 vTaskSwitchContext
      0.04%        2 TIM_Cmd
      0.02%        1 prvAddCurrentTaskToDelayedList
      0.02%        1 xTaskResumeAll
      0.02%        1 vTaskDelay
      0.02%        1 PendSV_Handler
      0.02%        1 __ISB
      0.02%        1 taskIn
      0.02%        1 statsGetRTVal
      0.02%        1 taskOut
    -----------------
                4400 Samples

orbtop can also generate graph output. You will find utilities to support this for
gnuplot in the `Support` directory.  Just start orbtop with the option `-o <filename>`
to generate the output data and then run `Support/orbtop_plot` to generate the output.
By default it generates pdf graphs once per second, but that's easily changed.

Dogfood
=======

Orbuculum was pointed at a a BMP instance (running on a 72MHz
STM32F103C8) both with and without SWO running in asynchronous mode at
2.25Mbps.

Firstly, without SWO;

     26.96%     1186 gdb_if_update_buf
     23.23%     1022 stm32f103_ep_read_packet
     21.82%      960 gdb_if_getchar_to
      6.66%      293 cdcacm_get_config
      6.54%      288 platform_timeout_is_expired
      5.61%      247 usbd_ep_read_packet
      4.86%      214 platform_time_ms
      3.90%      172 cdcacm_get_dtr
      0.13%        6 _gpio_clear
      0.06%        3 gpio_set_mode
      0.04%        2 swdptap_turnaround
      0.04%        2 swdptap_seq_out
      0.02%        1 swdptap_bit_in
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
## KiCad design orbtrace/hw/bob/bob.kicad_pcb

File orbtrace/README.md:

ORBTrace Development
====================

This is the development status for the ORBTrace parallel TRACE hardware. You're only here 'cos you're brave. This is built using Claire Wolfs' icestorm toolchain and currently targets a either a lattice iCE40HX-8K board or an Lambda Concept ECPIX-5 board (by default a -85F, but that's a trivial change in the makefile).

This is now complete (2nd February 2021). In theory, on an ECP5  or ICE40 HX8 part, it will work with any trace port operating up to at least 106MHz. Some stroking of the logic may make it a bit faster but there's no point doing that until everything else is done.  UP5K will run there up to around 50MHz, but if you're going out to buy something to use for running this code, that shouldn't be your first choice (ECPIX-5 should be, at least for now).

This should all be viewed as experimental. There remains work to be done....but see at the foot of this note. There are now two distinct families of builds; Verilog builds that build the whole stack and rely on the ftdi UART for communicaton, and nmigen builds that use an external ULPI for USB2-HS comms. You really want the nmigen USB2-HS version if you'e got a choice.

Note that ICE40HX1 support has been removed as it was just too snug to fit in the chip. The last version with (experimental) support for that chip can be found at https://github.com/orbcode/orbuculum/commit/58e7c03581231e0a37549060603aed7831c37533

Outstanding development actions;

 * Parse TPIU packets to split out ETM data and buffer it on-chip (will allow for post-mortem dumps)
 
Current testing status;

 * Tested on ICE40HX8K and ECPIX-5 at 1, 2 & 4 bit depths
 * Tested against Rising Edge and Falling edge synced flows
 * Tested with STM32F427 CPU running at 16MHz & 160MHz.
 * Tested with NRF5340 running at 32MHz

 * Needs testing at higher speeds and on more CPUs...this will be here forever, I guess

Verilog Builds
==============

This section is applicable to the ICE40HX8K, ICEBREAKER and ECPIX_5 boards.  It will result in comms over the ftdi link using either UART or SPI based communication. Note that SPI is faster, but only available on the ICE40.

To build it perform;

```
cd src
make ICE40HX8K_B_EVN

```
or;

```
cd src
make ECPIX_5_85F

```
or;
```
cd src
make ICEBREAKER
```

One the ICE40HX8 For normal operation you can burn the program image into the configuration serial memory
(J7:1-2, J6:2-4, and J6:1-3). For development just load it directly (J6:1-2 and
J6:3-4. Jumper J7 not installed). See Pg. 5 of the iCE40HX-8K Breakout Board User's Guide for
more information.

The ice40 breakout board is connected to the target via J2 as follows;

   * traceDin[0] C16
   * traceDin[1] D16
   * traceDin[2] E16
   * traceDin[3] F16
   * traceClk    H16

The ECPIX-5 is connected to the target via PMOD7 as follows;

   * traceDin[0] 0
   * traceDin[1] 1
   * traceDin[2] 2
   * traceDin[3] 3
   * traceClk    4

Make your grounds as good as possible...if you can twist a ground and clock together that will be helpful. Obviously you don't need the whole of traceDin[0..3] if you're only using 1 or 2 bit trace.

For ICE40 the system can be built using either an SPI or a UART transport layer. SPI is potentially capable of better performance (30MHz line rate). Testing shows that around 26Mbps is realistically acheivable. Both the serial and SPI interfaces are fully tested on ICE40.

For ECP5 only UART is supported at the moment since the hardware doesn't support the SPI...but you've also got the choice of ULPI for that.

Using UART data is presented at 12Mbaud over the serial port of the board. You can simply copy the frames of data to somewhere with something like this;

```
cat /dev/ttyUSB1 > myfile
```
Note that all syncs are removed from the data flow, which allows you to convey a lot more _real_ data. By default a sync is inserted every now and again, which keeps the UI sync'ed with the board.

Information on how to integrate it with orbuculum (hint, the `-o` option) is in the main README. Basically, you need to tell it that you're using the TRACE hardware and which serial port it appears on, like this;

```
ofiles/orbuculum -o 4 -p /dev/ttyUSB1
```

The value of the `-o` parameter sets the 'width' (i.e. number of bits) on the trace port hardware. If you include the `-m 100` kind of option it'll tell you how full the link is too. We sneak some other data into those sync packets from the board, so you will also see how many 16 byte frames of data have been received and the board LED status too, something like this;

```
1.5 MBits/sec (  51% full) LEDS: d--h Frames: 1903
```

The leds are `d`ata, `t`ransmit, `O`verflow and `h`eartbeat. Higher verbosity levels will report more link information, but that's mostly for debug and diagnostic purposes.

Once it's up and running you can treat it just like any other orbuculum data source. Note that you do need to set parallel trace, as opposed to SWO mode, in your setup. If you're using the gdbtrace.init file provided as part of orbuculum then this works fine for a STM32F427;

```
source ~/Develop/orbuculum/Support/gdbtrace.init

target remote localhost:2331
file ofiles/tracemule.elf
set mem inaccessible-by-default off
set print pretty
monitor reset
load
monitor reset

# This line for parallel trace output
enableSTM32TRACE 4

# For NRF53 use 'enableNRF53TRACE 4' instead

dwtSamplePC 1
dwtSyncTap 1
dwtPostTap 1
dwtPostInit 1
dwtPostReset 10
dwtCycEna 1
dwtTraceException 1

ITMId 1
ITMGTSFreq 0
ITMTSPrescale 3
ITMTXEna 1
ITMSYNCEna 1
ITMEna 1
ITMTSEna 0
ITMTER 0 0xFFFFFFFF
ITMTPR 0xFFFFFFFF
```

Note that signal integrity is a _huge_ issue. the `enableSTM32TRACE` command takes a second parameter which is drive strength, value 0-3. It defaults to 1. You may have to increase this.  If you have unexpected data corruption rest a finger on the TRACE input pins. If that fixes the issue, you know where it lies.  This will be addressed on 'production' hardware.

LEDs
====

 - ICE40:D2, ECPIX-5:LD5-Green: Heartbeat. Solid red when the bitfile is loaded. Flashes while the trace collector is running. (`h` in the `orbuculum` monitor)
 - ICE40:D4, ECPIX-5:LD6-Red: Overflow. Illuminated when there are too many data arriving over the trace link to be stored in local RAM prior to transmission (i.e. the off-board transmission link can't keep up), `O` in the monitor.
 - ICE40:D5, ECPIX-5:LD7-Blue: FallingEdge. (Diagnostic). Used to indicate that the link is synced to the falling edge rather than the rising one. Completely unimportant to end users, but very important to me...I will ask you for the state of this LED if you need support!
 - ICE40:D8, ECPIX-5:LD6-Green: Tx. Flashes while data is being sent over the serial link, `t` in the monitor.
 - ICE40:D9, ECPIX-5:LD8-Blue: Data. A 'sticky' version of D8 which will stay illuminated for about 0.7Secs after any data, `d` in the monitor.

ULPI Builds
===========

This is the preferred route since it offers much faster comms. At the moment it's only available on the ECPIX-5-85F board. To use it;

```
cd orbtrace/nmigen
python3 orbtrace_builder.py
```

...the image will be built and installed onto a connected ECPIX-5. By default it will burn the image to RAM. You will need to edit the build scripts to burn to flash (not advisable for now).

`orbuculum` will detect the Orbtrace board automatically, so no command line options are mandatory to use it.

IT IS VERY EXPERIMENTAL. CATS ARE AT RISK.

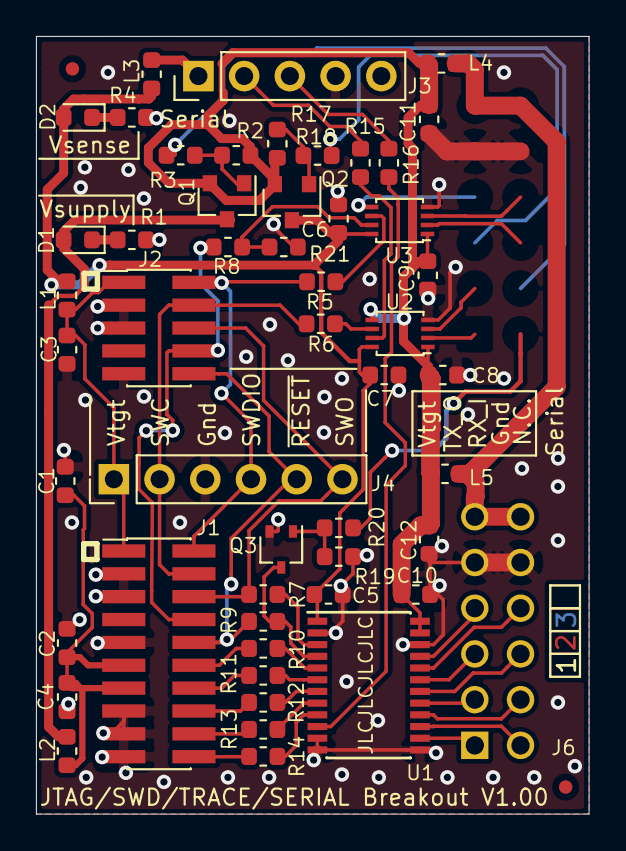
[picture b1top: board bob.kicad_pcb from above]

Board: 2 copper layers, 30.7 x 43.2 mm, 53 parts (0 on the bottom side), 45 nets.

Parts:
C1, C3, C11, C12: 10uF; C_0603_1608Metric
C2, C4: 10nF; C_0603_1608Metric
C5, C6, C7, C8, C9, C10: 100nF; C_0603_1608Metric
D1, D2: LED; LED_0603_1608Metric
FID1, FID2: Fiducial; Fiducial_0.75mm_Mask1.5mm
J1: DEBUG+TRACE HEADER; PinHeader_2x10_P1.27mm_Vertical_SMD
J2: DEBUG HEADER; PinHeader_2x05_P1.27mm_Vertical_SMD
J3: SERIAL HEADER; PinHeader_1x05_P2.54mm_Vertical
J4: DISCO HEADER; PinHeader_1x06_P2.54mm_Vertical
J6: PMOD2; pmod_pin_array_6x2
L1, L2, L3, L4, L5: CBG160808U301T; L_0603_1608Metric
Q1, Q2: Si2301CDS; SOT-23
Q3: DMG1012UW; SOT-323_SC-70
R1, R4: 1K; R_0603_1608Metric
R2, R17, R19: 10K; R_0603_1608Metric
R3, R5, R6, R7, R8, R9, R10, R11, R12, R13, R14, R15, R16, R18, R20: 100R; R_0603_1608Metric
R21: 100K; R_0603_1608Metric
U1: 74LVCH8T245; TSSOP-24_4.4x7.8mm_P0.65mm
U2, U3: SN74LVC2T45DCUR; VSSOP-8_2.4x2.1mm_P0.5mm

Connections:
+3V3: C8.2, C9.2, C10.2, C11.1, C12.1, L4.1, L5.1, Q1.2, Q2.2, R2.2, R17.2, U1.23, U1.24, U2.1, U2.5, U3.1
/MUXDIR: J6.4, U3.5
/RESETEN: J6.7, R20.1
/RXD_IN: J3.3, R16.2
/TCK_SWCLK: J1.4, J2.4, J4.2, R6.2
/TDI: J1.8, J2.8, R8.2
/TDO_SWO: J1.6, J2.6, J4.6, R7.2
/TMS_SWDIO: J1.2, J2.2, J4.4, R5.2
/TRACECLK: J1.12, R10.2
/TRACEDAT[0]: J1.14, R11.2
/TRACEDAT[1]: J1.16, R12.2
/TRACEDAT[2]: J1.18, R13.2
/TRACEDAT[3]: J1.20, R14.2
/TXD_OUT: J3.2, R15.2
/bxTCK_SWCLK: J6.2, U2.3
/bxTDI: J6.9, U3.2
/bxTMS_SWDIO: J6.10, U3.3
/bxTXD_OUT: J6.1, U2.2
/xRXD_IN: R16.1, U1.10
/xTCK_SWCLK: R6.1, U2.6
/xTDI: R8.1, R21.1, U3.7
/xTDO_SWO: R7.1, U1.3
/xTMS_SWDIO: R5.1, U3.6
/xTRACECLK: R10.1, U1.5
/xTRACEDAT0: R11.1, U1.6
/xTRACEDAT1: R12.1, U1.7
/xTRACEDAT2: R13.1, U1.8
/xTRACEDAT3: R14.1, U1.9
/xTXD_OUT: R15.1, U2.7
/~RESET: J1.10, J2.10, J4.5, R9.2
/~VDRIVEEN: J6.3, R18.1
/~VSEN: J6.8, R3.1
/~xRESET: Q3.3, R9.1, U1.4
GND: C1.1, C2.2, C3.2, C4.1, C5.2, C6.1, C7.2, C8.1, C9.1, C10.1, C11.2, C12.2, J1.3, J1.5, J1.9, J1.15, J1.17, J1.19, J2.3, J2.5, J2.9, J3.4, J4.3, J6.5, J6.11, Q3.2, R1.1, R4.1, R19.1, R21.2, U1.2, U1.11, U1.12, U1.13, U1.22, U2.4, U3.4
unnamed: C1.2, C2.1, C4.2, J1.11, J1.13, L2.2
unnamed: C3.1, J1.1, J2.1, J4.1, L1.2
unnamed: D1.1, R1.2
unnamed: D2.1, R4.2
unnamed: J3.1, L3.1
unnamed: J6.6, J6.12, L4.2, L5.2
unnamed: Q1.1, R2.1, R3.2
unnamed: Q2.1, R17.1, R18.2
unnamed: Q3.1, R19.2, R20.2
VS: D1.2, L2.1, Q1.3
Vdrive: C5.1, C6.2, C7.1, D2.2, L1.1, L3.2, Q2.3, U1.1, U2.8, U3.8

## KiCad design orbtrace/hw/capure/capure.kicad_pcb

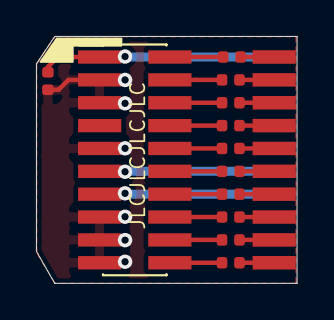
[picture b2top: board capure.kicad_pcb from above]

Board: 2 copper layers, 14.5 x 13.7 mm, 13 parts (0 on the bottom side), 24 nets.

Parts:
C1: 1uF; C_0402_1005Metric
J1: DEBUG+TRACE HEADER; pin_header
J2: DEBUG+TRACE HEADER; PinHeader_2x10_P1.27mm_Vertical_SMD
R1, R2, R3, R4, R5, R6, R7, R8, R9, R10: 100R; R_0402_1005Metric

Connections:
/TCK_SWCLK: J1.4, R2.2
/TDI: J1.8, R4.2
/TDO_SWO: J1.6, R3.2
/TMS_SWDIO: J1.2, R1.2
/TRACECLK: J1.12, R6.2
/TRACEDAT[0]: J1.14, R7.2
/TRACEDAT[1]: J1.16, R8.2
/TRACEDAT[2]: J1.18, R9.2
/TRACEDAT[3]: J1.20, R10.2
/xTCK_SWCLK: J2.4, R2.1
/xTDI: J2.8, R4.1
/xTDO_SWO: J2.6, R3.1
/xTMS_SWDIO: J2.2, R1.1
/xTRACECLK: J2.12, R6.1
/xTRACEDAT0: J2.14, R7.1
/xTRACEDAT1: J2.16, R8.1
/xTRACEDAT2: J2.18, R9.1
/xTRACEDAT3: J2.20, R10.1
/~RESET: J1.10, R5.2
/~xRESET: J2.10, R5.1
GND: C1.1, J1.3, J1.5, J1.9, J1.15, J1.17, J1.19, J2.3, J2.5, J2.9, J2.15, J2.17, J2.19
unnamed: C1.2, J1.1, J2.1
unnamed: J1.11, J2.11
unnamed: J1.13, J2.13

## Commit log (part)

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2022-07-10 Added long options for orbdump
2022-07-10 Added `-V`/`--version` for orbdump
2022-07-10 Type fix for _processOptions() in orbcat
2022-07-10 Added `-V`/`--version` for orbmortem
2022-07-10 Argument consistency for orbmortem
2022-07-10 Argument consistency for orbfifo
2022-07-10 Type fix for _processOptions() in orbfifo
2022-07-10 Type fix for _processOptions() in orbmortem
2022-07-10 Argument consistency for orbstat
2022-07-10 Argument consistency for orbprofile
2022-07-10 Added long options for orbstat
2022-07-10 Help argument consistency for orbprofile
2022-07-10 Added long options for orbprofile
2022-07-10 Help argument consistency for orbtrace
2022-07-10 Added ourself to the contributors file
2022-07-11 Change trace setup option to be -T
2022-07-11 Improve error reporting
2022-07-11 Stop makefile triggering rebuilds do to git tag, and add install/uninstall capabilities
2022-07-11 Documentation to support longopts & small option fixes
2022-07-12 Remove {function,data}-sections compile option
2022-07-18 Fix for memory allocation for non-usb interfaces
2022-07-20 After -fanalyser run and with issues resolved
2022-07-21 Fix orbfifo to connect correctly with streams abstraction
2022-07-21 Make orbstat compile on Win32
2022-07-21 orbstate: fix infinite receive loop
2022-07-21 Make orbdump work on Win32
2022-07-21 Small fixes to address edge use cases
2022-07-21 Prettyprinting and addition of health warning to orbprofile
2022-07-23 Fix MSG_NOSIGNAL on Win32
2022-07-23 New, more efficient, TPIU framer and decoder. Only implemented in orbuculum so far.
2022-07-24 Complete new TPIU decoder (5% CPU reduction in orbuculum)
2022-07-25 Documentation updates
2022-08-08 orbzmq: For raw channel send only used bytes
2022-08-18 Small tidy and switch to release build by default
2022-08-19 Allow run specification of orbtrace command line on orbuculum command line
2022-08-21 Add ncurses to linux build dependencies
2022-08-22 Fix handling of -v when no parameter is given
2022-08-22 Fix windows build
2022-08-25 Move to shared library and reduce binary sizes
2022-08-26 Move colour support over to terminfo for better portability
2022-08-26 meson + Windows
2022-08-26 Revert "Migration from pthreads to C11 threads"
    This reverts commit f66e4f9c338414dd86650fe6a89d391cd6d4a91e.
2022-08-26 meson/Windows: install system libraries
2022-08-26 Adjust maximum usb transfer buffer size
2022-08-27 Move to condition variables and away from mutex for IPC
2022-08-29 Only unwind to target exception on resume
2022-08-29 orbtop: separately account for interrupt wall time and show interrupt utilization percent
    At each exception nesting level, track the time "stolen" by a nested interrupt.
    Use this to compute the wall time (total time including nested interrupts), and show
    the maximum at each interval. This is useful in trying to gauge worst case execution
    time. Additionally, show a percentage of time spent each interval in every exception.
2022-08-29 Update for alphabetic order
2022-08-30 Remove library dependency on curses/terminfo
2022-08-30 Prettyprinting
2022-09-03 Initial Python client support
2022-09-04 Use Meson for CI builds
2022-10-04 fix: macOS doesn’t support unnamed POSIX semaphores
2022-11-02 Update windows build process
2022-11-02 Fix to prettyprinting issue identified in #92
2022-11-02 Updated Windows build instructions in README
2022-11-23 Small fixes to address verbosity
2022-12-01 Fix linux workflow
2022-12-01 Add SDL to MinGW dependencies
2022-12-06 Prevent delay on close
2022-12-06 Rendering quality improvement
2022-12-07 s/ORBLCD_DECODE_X/ORBLCD_DECODE_Y/
    Avoids memset() stomping past the end of the pixel buffer.
2023-04-11 Improve monotonicity of orbtop results
2023-04-11 Fix orbcat format specifiers, addressing #95
2023-04-11 Make workflow correctly recognise bin files
2023-05-01 Addition of timestamping to orbcat
2023-05-17 Simplfy timing improvement code
2023-05-18 Improvements to interval timing, WIP
2023-05-20 Better multiprobe differentiation, better libusb robustness
2023-05-21 Improve shutdown handling for terminate on completion case
2023-05-25 WIP:Initial refactoring to support ETM4.
2023-06-04 fix: Orbuculum use stream abstraction for accessing nwserver
    Orbuculum was still using POSIX API directly instead of stream
    abstraction. That means it was using read() for receiving data from
    sockets which is not valid on Win32.
    Direct POSIX API usage was replaced with stream abstraction bringing
    back receiving data from TCP upstream (e.g. J-Link GDB Server) on Win32
2023-06-30 WIP:snapshot
2023-07-02 Addition of configuration of ETM4 macrocell
2023-07-13 WIP: Slightly less crashy, still no working call stacking
2023-07-13 WIP: Call stacking now working. Just interrupt returns (and specifically pop lr) to sort
2023-07-16 update CONTRIBUTORS
2023-07-16 Add note about changing install path
2023-07-18 Fix incorrect jump calculation
2023-07-21 Add explicit language for the duration of commands and formatting
2023-07-27 Do not report deprecated declarations as errors.
    Libusb at some point in time marked libusb_init as deprecated (they
    later undo the deprecation) which is reported as warning and treated as
    error failing build.
2023-07-27 Use localtime instead of localtime_r
    localtime_r is available from C23 (https://en.cppreference.com/w/c/chrono/localtime)
2023-07-29 Fix overflow in reporting data transfer rate in orbuculum
2023-07-29 Small improvements to source reading and move from Bps to bps in orbmortem status bar
2023-07-30 Update to libdwarf 0.7.0
    Based on
    https://github.com/tech2077/orbuculum/commit/9fe60cfee1e1d5912d2083556e879f08f0637182
    by https://github.com/tech2077
2023-07-30 Windows CI: add capstone dependency
2023-07-30 Addition of python based dwarf validation tool
2023-07-30 Fixes for linux
2023-08-01 Support O_BINARY for platforms that differentiate between binary and text files
2023-08-02 Fixes for orbfifo issues; inability to CTRL-C before connection, incorrect basedir specification and no provision for server and port setting
2023-08-04 Improve CPU utilisation
2023-08-07 Addition of experimental COBS decoder
2023-08-07 Remove malloc pragma warning for case of compilation under OSX
2023-08-07 OSX CI Builder Integration
2023-08-22 Addition of gdb init for imxrt1010
2023-08-22 Fix for compilation on Windows (lack of per-call non-blocking semantics)
2023-08-23 Improve data transfer reliability with remote clients
2023-08-25 Improved slow client handling
2023-08-26 Use select call on WIN32 rather than poll
2023-08-28 Switch to c++ compiler and changes for clean compilation
2023-08-31 Limit orb library dependencies
    Due to meson/mingw quirk liborb.dll was importing DllMain from
    libintl.dll. That's actually does not make much sense (each shared
    library should have their own entry point) and is additional
    but not used dependency for using liborb.dll.
    libintl is not specified directly in meson.build but by examining
    command line options passed to linker I determined that it is stated
2023-09-02 Next stage of COBS development, with TPIU channels in COBS frame header
2023-09-18 Basic testing of COBS flows done. In progress
2023-09-22 gdbtrace.init: Remove redundant stopETM definition.
2023-09-22 gdbtrace.init: Fix describeETM definition.
    Fixes #120
2023-09-28 Addition of gdb init for s32k344
2023-10-12 Force LF line endings in libdwarf patch
2023-10-27 Added instruction on how to install on Linux
2023-10-30 Respect the loadlines flag in symbolAquire
2023-10-30 Fix spelling of symbolAquire -> symbolAcquire
2023-11-04 Speed up line filtering for large codebases
2023-11-05 Cleaned up image aquisition
2023-11-16 Fix clang compilation of libdwarf on macOS 13
2023-12-09 Update to compile on FreeBSD.
2024-01-15 orbtop: fix cpu usage growth over time
    When we are finished with a set of seen addresses for an interval, make
    sure to flush the hash as well, not just free the report generated.
    Fixes: https://github.com/orbcode/orbuculum/issues/135
2024-01-19 loadelf: Fix use-after-free of Dwarf_Die pointer
2024-01-29 gdbtrace: add basic Kinetis SWO support
    Tested with K70, SWO only at this point.
2024-02-06 Get linkage name for mangled C++ symbols
2024-02-07 Add records for mangled names
2024-03-11 Fix to orbmortem file saving from Issue #141
2024-03-14 Working, largely untested, version. Beware changes to command line parameters in orbuculum related to TPIU
2024-03-16 Tested with experimental orbtrace COBS code
2024-04-01 Disconnect clients that take too long in processing
2024-04-17 Simplify different protocol handling, WIP
2024-05-26 Move to use of OTAG for protocol descriptor rather than COBS. Fix versioning of probe.
2024-06-02 build: Make libSDL2 optional and only link orblcd against it
    * Only orblcd requires libSDL2.
    * Allow building the command-line tools if libSDL2 is not found.
    * Don't link them all against libSDL2.
2024-06-03 orbmortem: missing include
2024-06-09 Improve handling of slow arriving usb packets to ensure orbtop accuracy + group probe types in multi-device listing
2024-06-09 Patch to allow build under windows CI
2024-06-15 Tidy up tag accounting
2024-06-15 Add system exception event reporting
2024-06-16 Cherry picked diff from ORBEXCEPTION for orbcat exception reporting
2024-06-16 Move from COBS to OTAG
2024-08-04 Move BMP endpoint to 3
    Endpoint has been changed recently.
    See
    https://github.com/blackmagic-debug/blackmagic/commit/6af8d5dc48d1ba0e8a0bb752bd40a4242d84765e
2024-08-05 Addition of checksum to OTAG packets
2024-08-06 Search for trace interface on BMP.
2024-08-06 gdbinits: Fix incorrect names in gdbinit-bmp
2024-08-07 Incoporate PR#149 to fix rusty naming
2024-08-09 add support for sam 5x mcu trace
2024-08-09 fix indentation
2024-08-12 Accomodate OTAG protocol identification on ORBTrace
2024-08-12 Results of review via cppcheck
2024-08-13 Add bind support for udev
2024-08-22 Additional command line option sanity checking
2024-08-22 Fix text typo (Nummber -> Number)
2024-08-23 Fix minimum report interval time
2024-08-23 Fix minimum channel number
2024-08-25 Add support for TPIU encoded orbflow channel 1
2024-08-27 update artifact action to v4
2024-08-28 Update ORBFLOW file header
2024-08-30 Rebase of cobs on main and minor fixups
2024-09-02 Remove TPIU from client utilities and test
2024-09-04 Update workflow version
2024-09-04 Improve documentation and command line consistancy
2024-09-09 Report (at higher verbosity levels) when client disconnects
2024-09-20 Add COBS draining state to ensure fast resync
2024-10-19 Fix C++ function names cut too early
2024-10-24 TraceDecoder
    add overflow debug parameter
2024-10-24 _processFunctionDie fix
2024-10-27 Fix redundant access to DBGMCU for SAMD5 per issue #157
2024-11-29 Avoid memory leak
2024-11-29 Prettyprint fixups
2024-12-18 Explicitly print any address that doesn't match
2024-12-21 Make protocol spec mandatory in orbtop when source is set
2025-01-03 Now with added testing
2025-02-12 Update changes to reflect gitlog
2025-02-17 Fix M33 type detection
2025-02-17 Add support for STM32H7 in gdbtrace.init
2025-02-17 Introduce unlockComponent
2025-02-17 Unlock DWT instead of ETM in prepareSWO
2025-02-27 Extend from-target timestamping to 1/10us resolution
2025-03-14 Fix all code to have more sensible differentiation between stdout and stderr
2025-03-28 Make enableSTM32TRACE have sensible default
2025-03-31 Improve lcd handling for ETC
2025-04-17 Increase max string length in a single packet
2025-04-21 Remove orbfifo from build as its no longer relevant
2025-09-09 Added orbtop-rtos
2025-09-09 Some documentation
2025-12-10 Fix: define correct mask for interrupts
    orbstat detects interrupts by comparing LR values to the SPECIALS_MASK.
    Correct the mask to fit also armv8-m and armv7-m architecture.
